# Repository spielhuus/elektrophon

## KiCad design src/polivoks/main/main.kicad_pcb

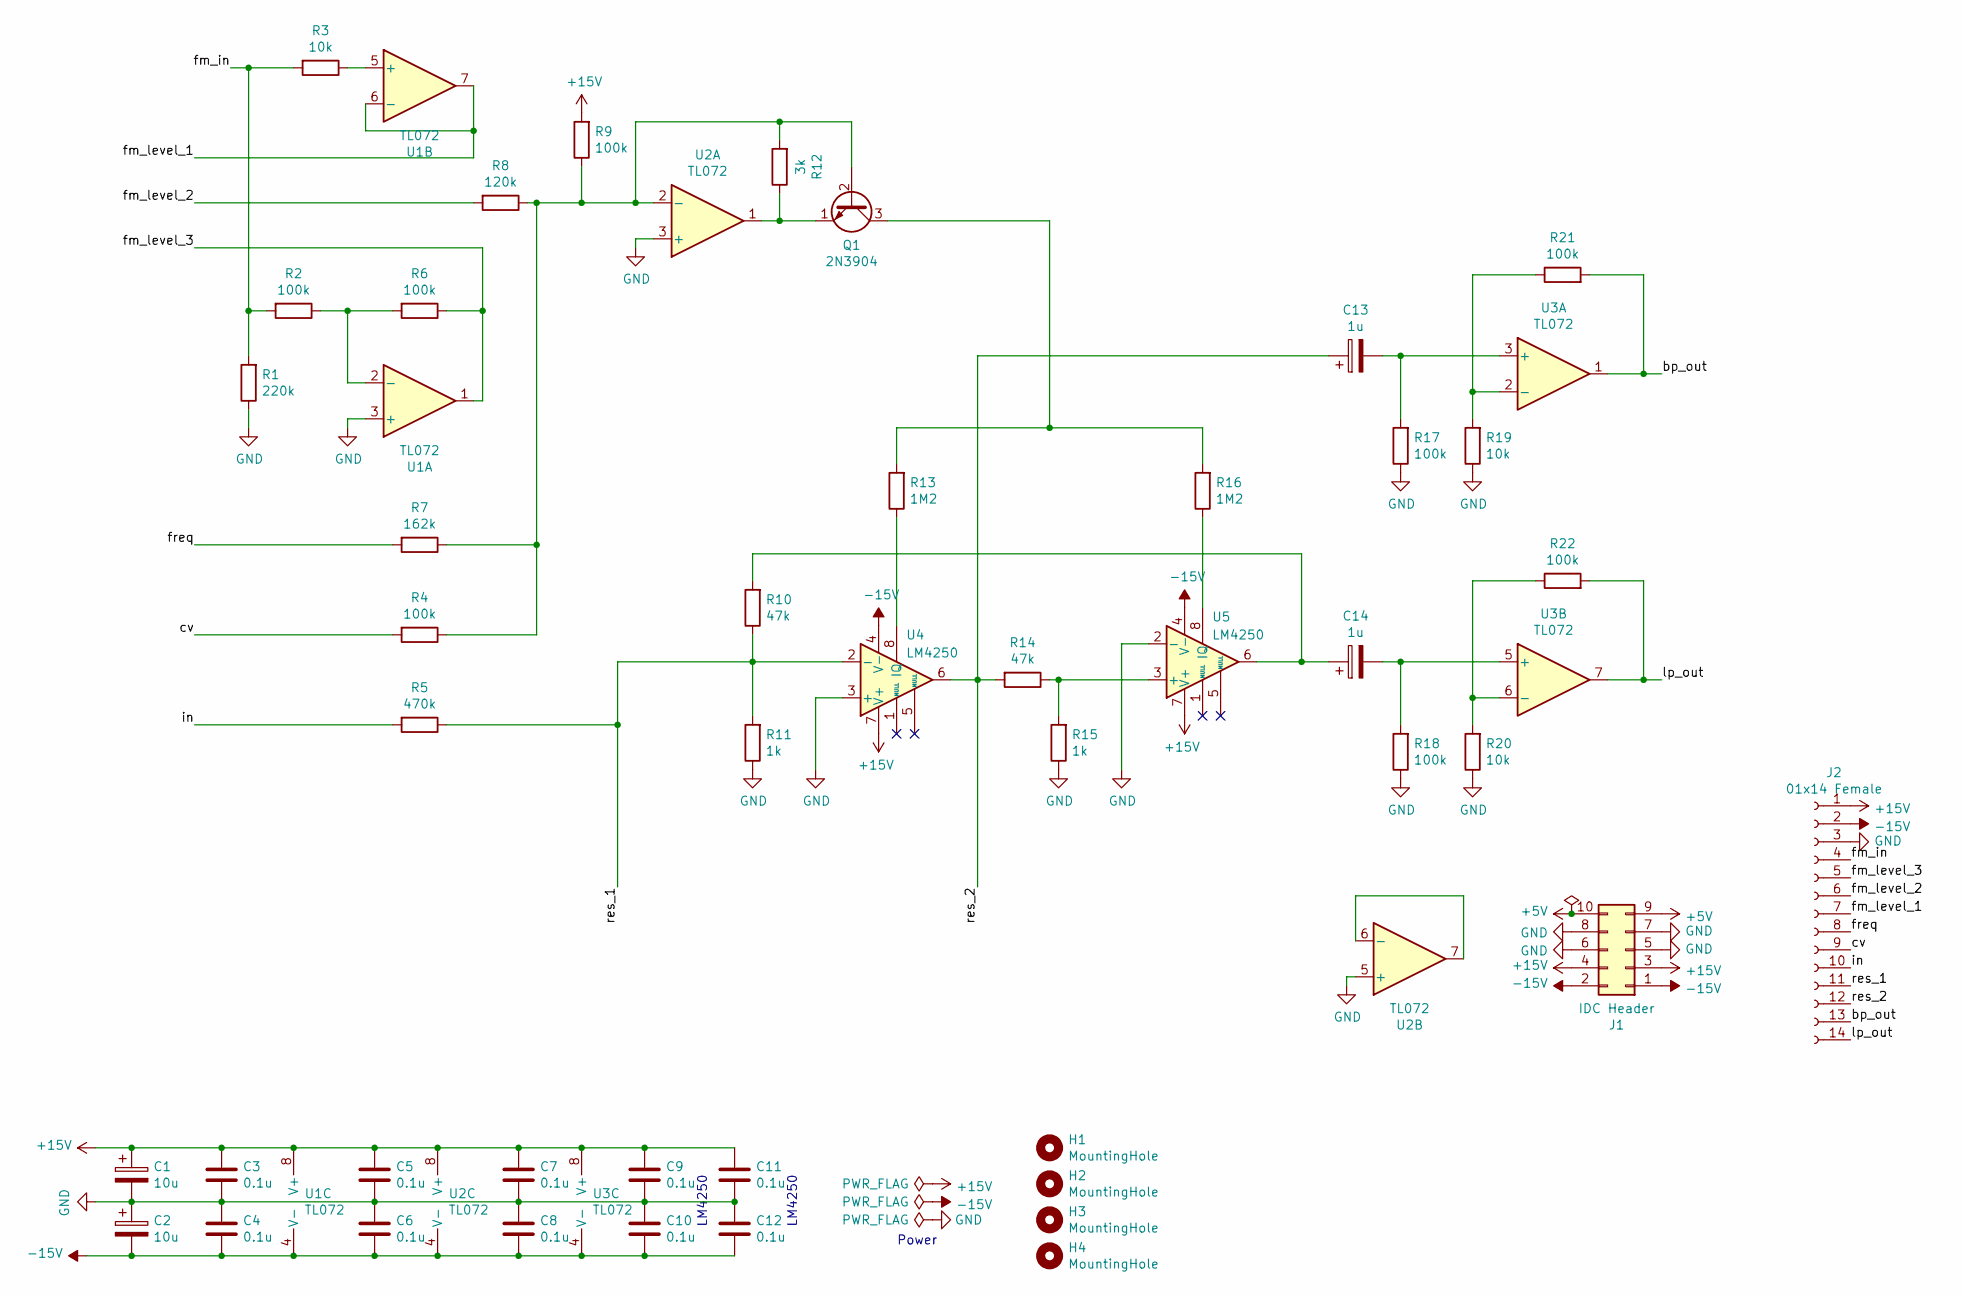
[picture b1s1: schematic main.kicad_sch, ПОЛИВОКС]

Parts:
C1, C2: 10u; CP_Radial_D5.0mm_P2.50mm
C3, C4, C5, C6, C7, C8, C9, C10, C11, C12: 0.1u; C_Disc_D3.4mm_W2.1mm_P2.50mm
C13, C14: 1u; CP_Radial_D5.0mm_P2.00mm
H1, H2, H3, H4: MountingHole; MountingHole_2.2mm_M2
J1: IDC Header; IDC-Header_2x05_P2.54mm_Vertical
J2: 01x14 Female; PinSocket_1x14_P2.54mm_Vertical
Q1: 2N3904; TO-92_Inline_Wide
R1: 220k; R_Axial_DIN0207_L6.3mm_D2.5mm_P10.16mm_Horizontal
R2, R4, R9, R17, R18: 100k; R_Axial_DIN0207_L6.3mm_D2.5mm_P10.16mm_Horizontal
R3, R19, R20: 10k; R_Axial_DIN0207_L6.3mm_D2.5mm_P10.16mm_Horizontal
R5: 470k; R_Axial_DIN0207_L6.3mm_D2.5mm_P10.16mm_Horizontal
R6, R21, R22: 100k; R_Axial_DIN0207_L6.3mm_D2.5mm_P2.54mm_Vertical
R7: 162k; R_Axial_DIN0207_L6.3mm_D2.5mm_P10.16mm_Horizontal
R8: 120k; R_Axial_DIN0207_L6.3mm_D2.5mm_P10.16mm_Horizontal
R10, R14: 47k; R_Axial_DIN0207_L6.3mm_D2.5mm_P10.16mm_Horizontal
R11, R15: 1k; R_Axial_DIN0207_L6.3mm_D2.5mm_P10.16mm_Horizontal
R12: 3k; R_Axial_DIN0207_L6.3mm_D2.5mm_P10.16mm_Horizontal
R13, R16: 1M2; R_Axial_DIN0207_L6.3mm_D2.5mm_P10.16mm_Horizontal
U1, U2, U3: TL072; DIP-8_W7.62mm_Socket
U4, U5: LM4250; DIP-8_W7.62mm_Socket

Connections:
+5V: J1.9, J1.10
+15V: C1.1, C3.1, C5.1, C7.1, C9.1, C11.1, J1.3, J1.4, J2.1, R9.2, U1.8 (V+), U2.8 (V+), U3.8 (V+), U4.7 (V+), U5.7 (V+)
-15V: C2.2, C4.2, C6.2, C8.2, C10.2, C12.2, J1.1, J1.2, J2.2, U1.4 (V-), U2.4 (V-), U3.4 (V-), U4.4 (V-), U5.4 (V-)
/bp_out: J2.13, R21.2, U3.1
/cv: J2.9, R4.2
/fm_in: J2.4, R1.2, R2.2, R3.2
/fm_level_1: J2.7, U1.6 (-), U1.7
/fm_level_2: J2.6, R8.2
/fm_level_3: J2.5, R6.1, U1.1
/freq: J2.8, R7.2
/in: J2.10, R5.2
/lp_out: J2.14, R22.2, U3.7
/res_1: J2.11, R5.1, R10.1, R11.2, U4.2 (-)
/res_2: C13.1, J2.12, R14.2, U4.6
GND: C1.2, C2.1, C3.2, C4.1, C5.2, C6.1, C7.2, C8.1, C9.2, C10.1, C11.2, C12.1, J1.5, J1.6, J1.7, J1.8, J2.3, R1.1, R11.1, R15.1, R17.1, R18.1, R19.1, R20.1, U1.3 (+), U2.3 (+), U2.5 (+), U4.3 (+), U5.2 (-)
unnamed: C14.1, R10.2, U5.6
unnamed: Q1.2 (B), R4.1, R7.1, R8.1, R9.1, R12.2, U2.2 (-)
unnamed: Q1.3 (C), R13.2, R16.2
unnamed: Q1.1 (E), R12.1, U2.1
unnamed: R2.1, R6.2, U1.2 (-)
unnamed: R3.1, U1.5 (+)
unnamed: U2.6 (-), U2.7
unnamed: C13.2, R17.2, U3.3 (+)
unnamed: R19.2, R21.1, U3.2 (-)
unnamed: C14.2, R18.2, U3.5 (+)
unnamed: R20.2, R22.1, U3.6 (-)
unnamed: R13.1, U4.8 (IQ)
unnamed: R14.1, R15.2, U5.3 (+)
unnamed: R16.1, U5.8 (IQ)

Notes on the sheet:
LM4250
Power

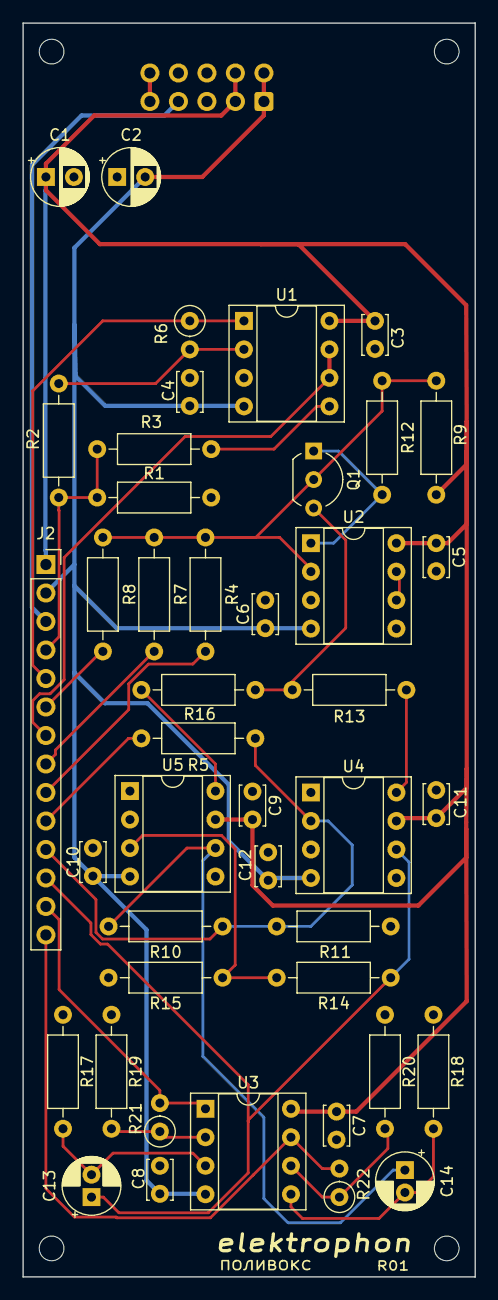
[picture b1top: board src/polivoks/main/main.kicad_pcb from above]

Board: 2 copper layers, 40.3 x 111.8 mm, 48 parts (1 on the bottom side), 29 nets.

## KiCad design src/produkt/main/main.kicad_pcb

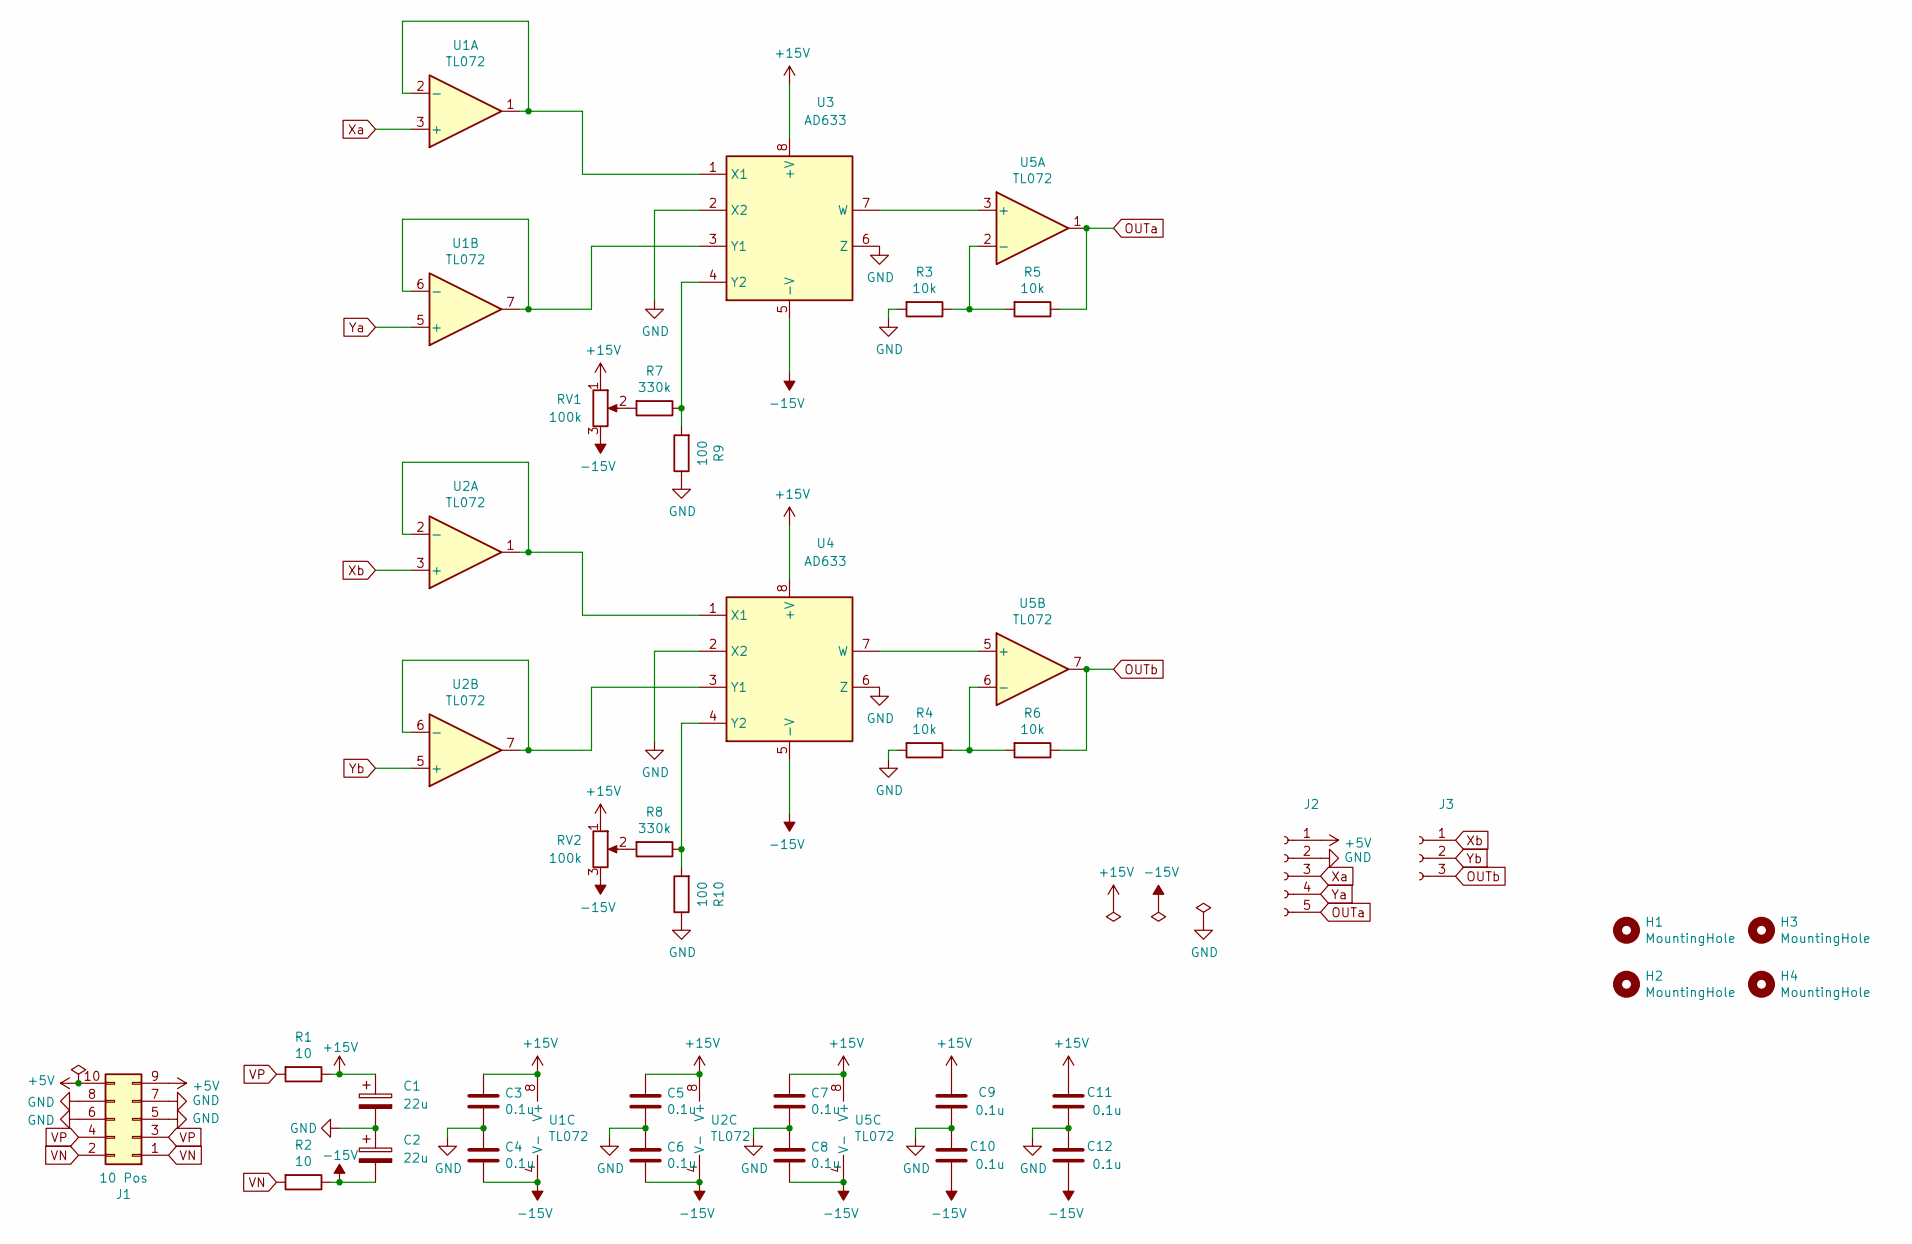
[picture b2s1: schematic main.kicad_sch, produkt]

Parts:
C1, C2: 22u; CP_Radial_D6.3mm_P2.50mm
C3, C4, C5, C6, C7, C8, C9, C10, C11, C12: 0.1u; C_Disc_D3.8mm_W2.6mm_P2.50mm
H1, H2, H3, H4: MountingHole; MountingHole_2.2mm_M2
J1: 10 Pos; IDC-Header_2x05_P2.54mm_Vertical
J2: 01x05 Female; PinSocket_1x05_P2.54mm_Vertical
J3: 01x03 Female; PinSocket_1x03_P2.54mm_Vertical
R1, R2: 10; R_Axial_DIN0204_L3.6mm_D1.6mm_P5.08mm_Horizontal
R3, R4, R5, R6: 10k; R_Axial_DIN0204_L3.6mm_D1.6mm_P5.08mm_Horizontal
R7, R8: 330k; R_Axial_DIN0204_L3.6mm_D1.6mm_P5.08mm_Horizontal
R9, R10: 100; R_Axial_DIN0204_L3.6mm_D1.6mm_P5.08mm_Horizontal
RV1, RV2: 100k; Potentiometer_Bourns_3386P_Vertical
U1, U2, U5: TL072; DIP-8_W7.62mm_Socket
U3, U4: AD633; DIP-8_W7.62mm

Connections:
+5V: J1.9, J1.10, J2.1
+15V: C1.1, C3.1, C5.1, C7.1, C9.1, C11.1, R1.1, RV1.1, RV2.1, U1.8 (V+), U2.8 (V+), U3.8 (+V), U4.8 (+V), U5.8 (V+)
-15V: C2.2, C4.2, C6.2, C8.2, C10.2, C12.2, R2.1, RV1.3, RV2.3, U1.4 (V-), U2.4 (V-), U3.5 (-V), U4.5 (-V), U5.4 (V-)
GND: C1.2, C2.1, C3.2, C4.1, C5.2, C6.1, C7.2, C8.1, C9.2, C10.1, C11.2, C12.1, J1.5, J1.6, J1.7, J1.8, J2.2, R3.2, R4.2, R9.1, R10.1, U3.2 (X2), U3.6 (Z), U4.2 (X2), U4.6 (Z)
unnamed: R7.2, RV1.2
unnamed: R8.2, RV2.2
unnamed: U1.1, U1.2 (-), U3.1 (X1)
unnamed: U1.6 (-), U1.7, U3.3 (Y1)
unnamed: U2.1, U2.2 (-), U4.1 (X1)
unnamed: U2.6 (-), U2.7, U4.3 (Y1)
unnamed: U3.7 (W), U5.3 (+)
unnamed: R7.1, R9.2, U3.4 (Y2)
unnamed: U4.7 (W), U5.5 (+)
unnamed: R8.1, R10.2, U4.4 (Y2)
unnamed: R3.1, R5.2, U5.2 (-)
unnamed: R4.1, R6.2, U5.6 (-)
OUTa: J2.5, R5.1, U5.1
OUTb: J3.3, R6.1, U5.7
VN: J1.1, J1.2, R2.2
VP: J1.3, J1.4, R1.2
Xa: J2.3, U1.3 (+)
Xb: J3.1, U2.3 (+)
Ya: J2.4, U1.5 (+)
Yb: J3.2, U2.5 (+)

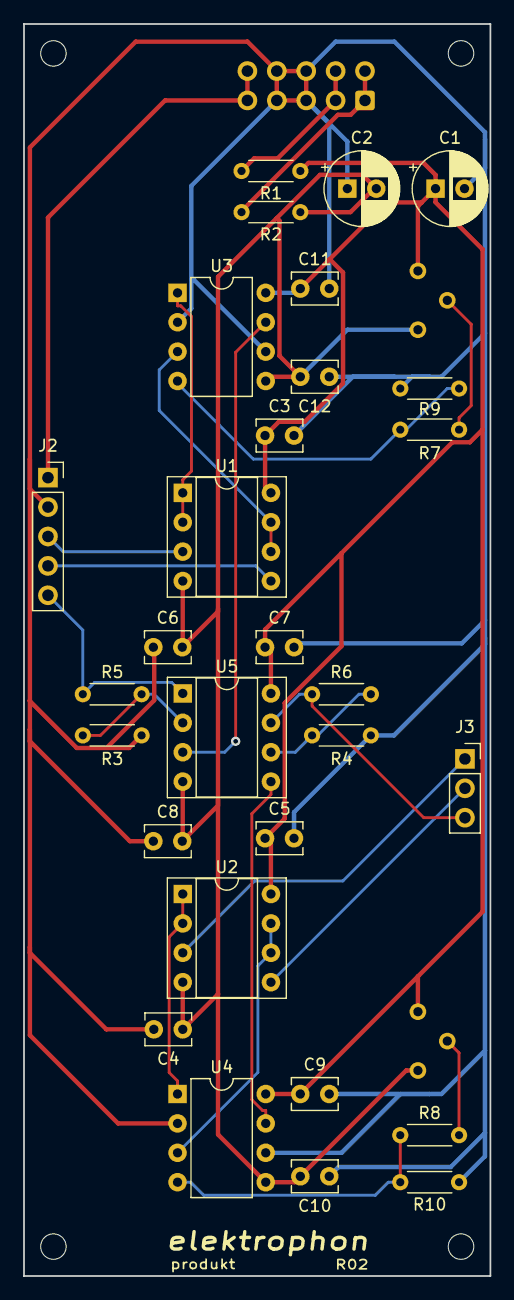
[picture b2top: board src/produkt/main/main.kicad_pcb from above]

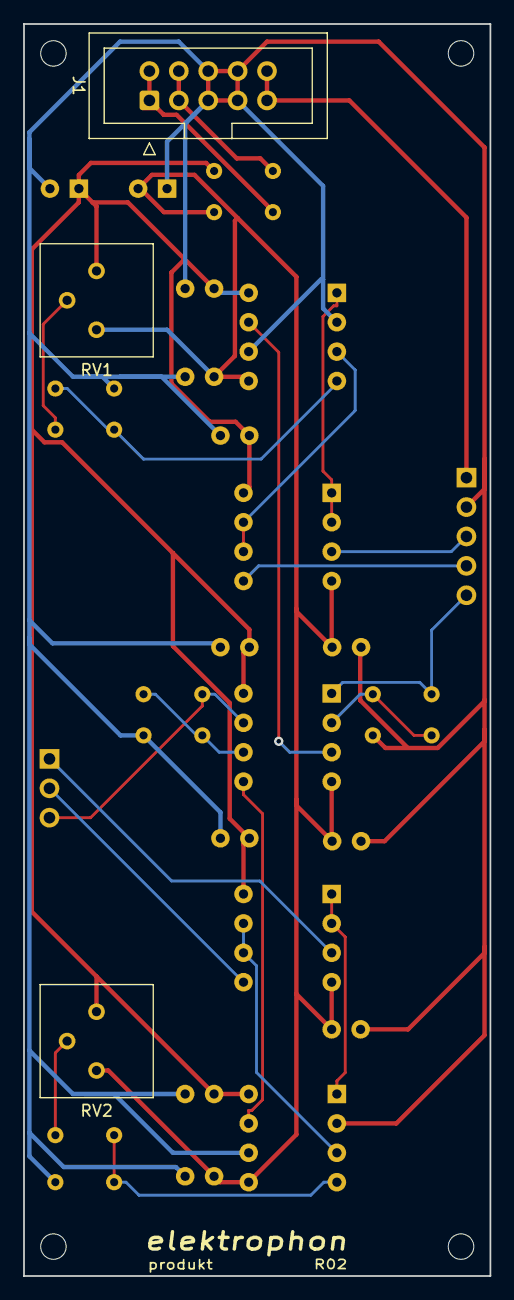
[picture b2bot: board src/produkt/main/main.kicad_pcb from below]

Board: 2 copper layers, 40.3 x 108.2 mm, 36 parts (3 on the bottom side), 24 nets.

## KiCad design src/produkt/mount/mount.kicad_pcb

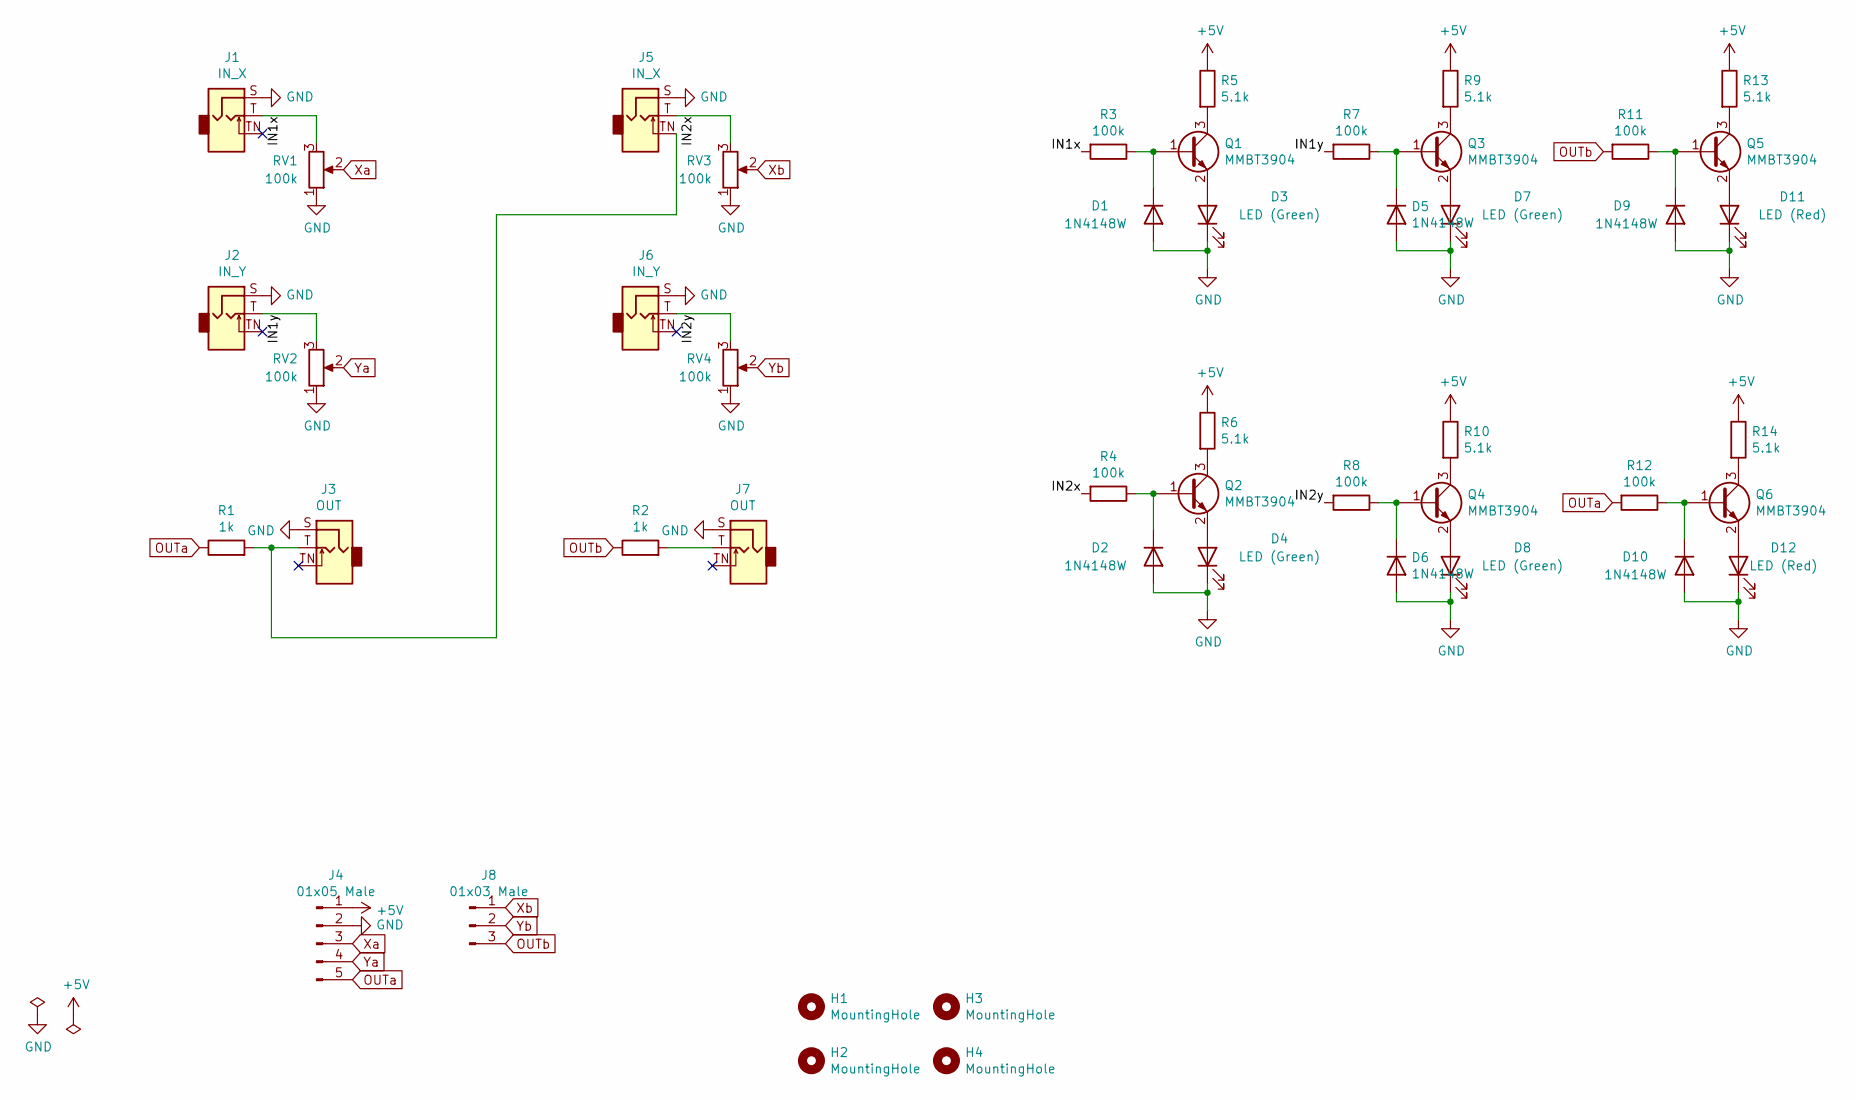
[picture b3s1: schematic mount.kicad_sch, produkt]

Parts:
D1, D2, D5, D6, D9, D10: 1N4148W; D_SOD-123
D3, D4, D7, D8: LED (Green); LED_D3.0mm
D11, D12: LED (Red); LED_D3.0mm
H1, H2, H3, H4: MountingHole; MountingHole_2.2mm_M2
J1, J5: IN_X; Jack_3.5mm_WQP-PJ398SM_Vertical
J2, J6: IN_Y; Jack_3.5mm_WQP-PJ398SM_Vertical
J3, J7: OUT; Jack_3.5mm_WQP-PJ398SM_Vertical
J4: 01x05 Male; PinHeader_1x05_P2.54mm_Vertical
J8: 01x03 Male; PinHeader_1x03_P2.54mm_Vertical
Q1, Q2, Q3, Q4, Q5, Q6: MMBT3904; SOT-23
R1, R2: 1k; R_Axial_DIN0204_L3.6mm_D1.6mm_P5.08mm_Horizontal
R3, R4, R7, R8, R11, R12: 100k; R_0805_2012Metric_Pad1.20x1.40mm_HandSolder
R5, R6, R9, R10, R13, R14: 5.1k; R_0805_2012Metric_Pad1.20x1.40mm_HandSolder
RV1, RV2, RV3, RV4: 100k; Potentiometer_Alpha_RD901F-40-00D_Single_Vertical

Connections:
+5V: J4.1, R5.1, R6.1, R9.1, R10.1, R13.1, R14.1
/IN1x: J1.T, R3.2, RV1.3
/IN1y: J2.T, R7.2, RV2.3
/IN2x: J5.T, R4.2, RV3.3
/IN2y: J6.T, R8.2, RV4.3
GND: D1.2 (A), D2.2 (A), D3.1 (K), D4.1 (K), D5.2 (A), D6.2 (A), D7.1 (K), D8.1 (K), D9.2 (A), D10.2 (A), D11.1 (K), D12.1 (K), J1.S, J2.S, J3.S, J4.2, J5.S, J6.S, J7.S, RV1.1, RV2.1, RV3.1, RV4.1
unnamed: D1.1 (K), Q1.1 (B), R3.1
unnamed: D2.1 (K), Q2.1 (B), R4.1
unnamed: D3.2 (A), Q1.2 (E)
unnamed: D4.2 (A), Q2.2 (E)
unnamed: D5.1 (K), Q3.1 (B), R7.1
unnamed: D6.1 (K), Q4.1 (B), R8.1
unnamed: D7.2 (A), Q3.2 (E)
unnamed: D8.2 (A), Q4.2 (E)
unnamed: D9.1 (K), Q5.1 (B), R11.1
unnamed: D10.1 (K), Q6.1 (B), R12.1
unnamed: D11.2 (A), Q5.2 (E)
unnamed: D12.2 (A), Q6.2 (E)
unnamed: J3.T, J5.TN, R1.2
unnamed: J7.T, R2.2
unnamed: Q1.3 (C), R5.2
unnamed: Q2.3 (C), R6.2
unnamed: Q3.3 (C), R9.2
unnamed: Q4.3 (C), R10.2
unnamed: Q5.3 (C), R13.2
unnamed: Q6.3 (C), R14.2
OUTa: J4.5, R1.1, R12.2
OUTb: J8.3, R2.1, R11.2
Xa: J4.3, RV1.2
Xb: J8.1, RV3.2
Ya: J4.4, RV2.2
Yb: J8.2, RV4.2

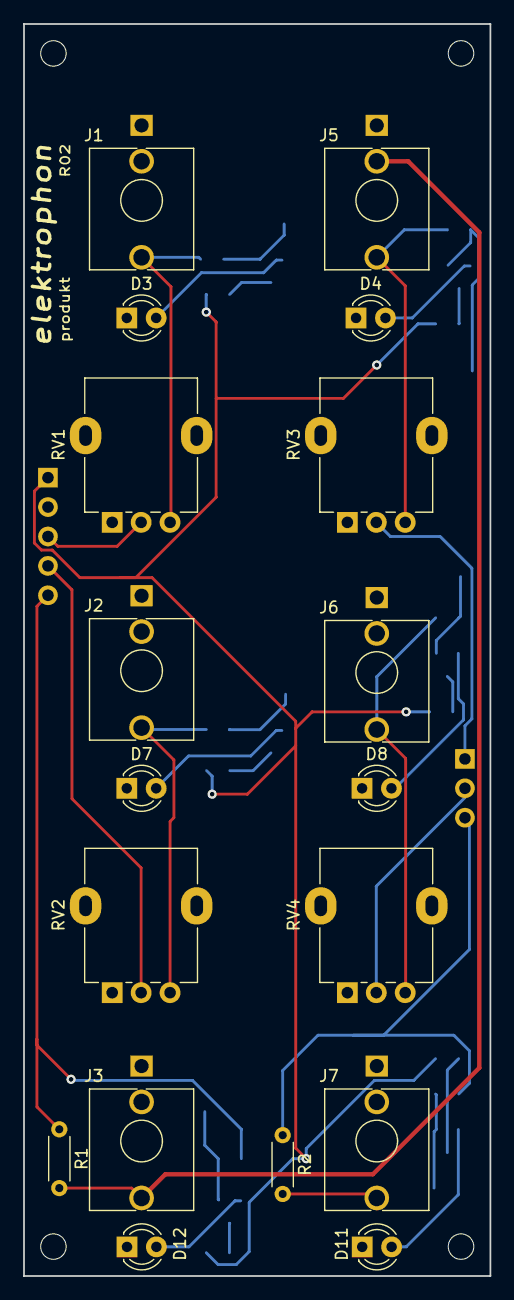
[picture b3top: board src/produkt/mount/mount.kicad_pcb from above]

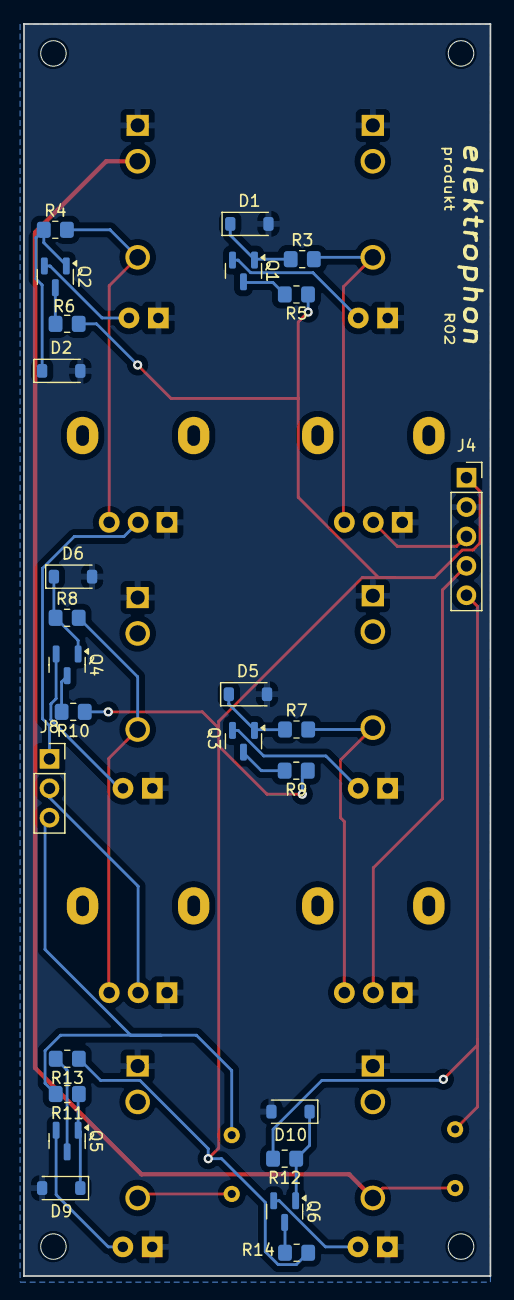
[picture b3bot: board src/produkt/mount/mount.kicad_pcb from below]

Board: 2 copper layers, 40.3 x 108.2 mm, 48 parts (26 on the bottom side), 32 nets.

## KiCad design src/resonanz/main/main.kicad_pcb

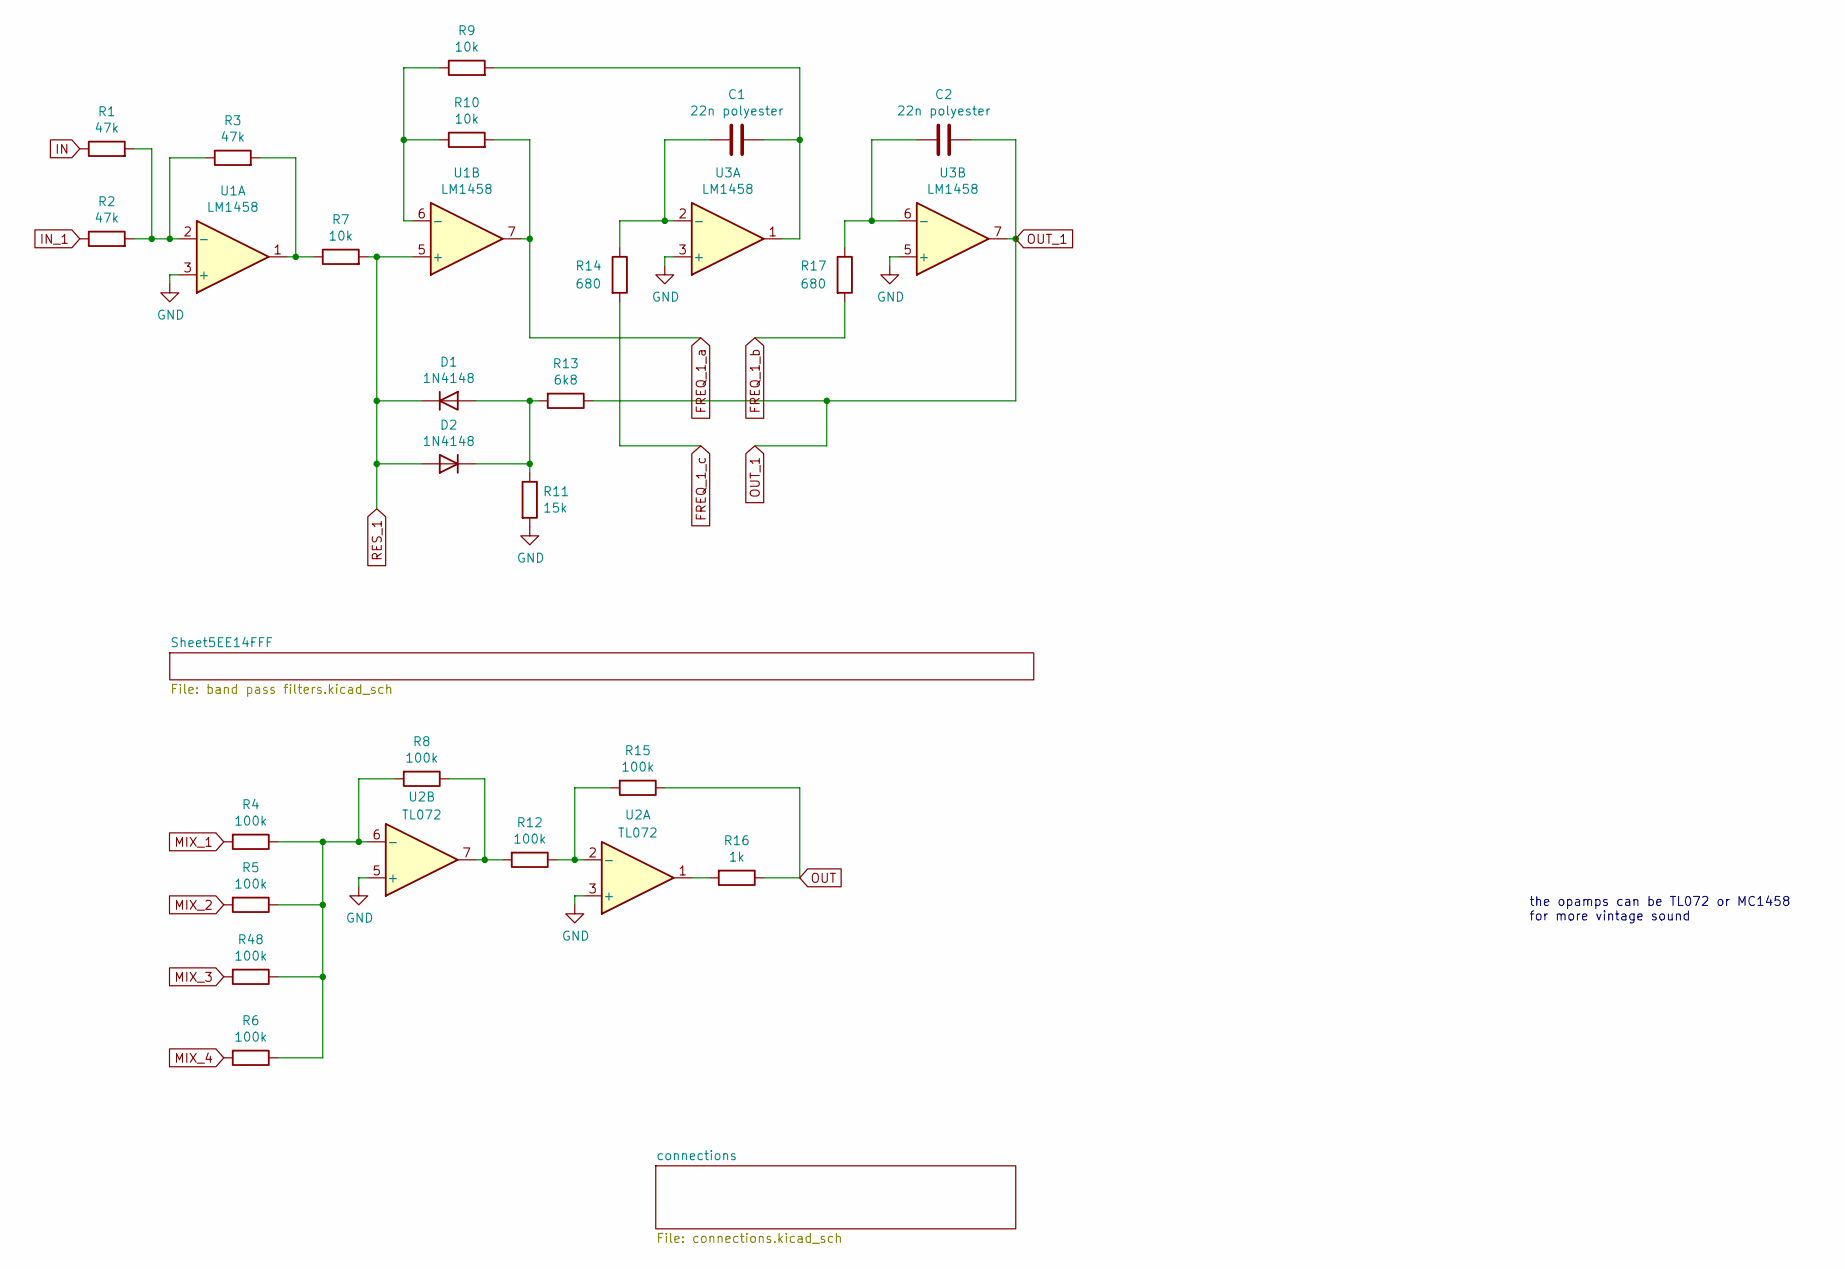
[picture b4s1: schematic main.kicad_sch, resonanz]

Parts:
C1, C2: 22n polyester; C_Rect_L7.2mm_W2.5mm_P5.00mm_FKS2_FKP2_MKS2_MKP2
D1, D2: 1N4148; D_DO-35_SOD27_P3.81mm_Vertical_KathodeUp
R1, R2: 47k; R_Axial_DIN0207_L6.3mm_D2.5mm_P10.16mm_Horizontal
R3: 47k; R_Axial_DIN0207_L6.3mm_D2.5mm_P2.54mm_Vertical
R4, R5, R6, R12, R15, R48: 100k; R_Axial_DIN0207_L6.3mm_D2.5mm_P10.16mm_Horizontal
R7: 10k; R_Axial_DIN0207_L6.3mm_D2.5mm_P10.16mm_Horizontal
R8: 100k; R_Axial_DIN0207_L6.3mm_D2.5mm_P2.54mm_Vertical
R9, R10: 10k; R_Axial_DIN0207_L6.3mm_D2.5mm_P2.54mm_Vertical
R11: 15k; R_Axial_DIN0207_L6.3mm_D2.5mm_P10.16mm_Horizontal
R13: 6k8; R_Axial_DIN0207_L6.3mm_D2.5mm_P2.54mm_Vertical
R14, R17: 680; R_Axial_DIN0207_L6.3mm_D2.5mm_P10.16mm_Horizontal
R16: 1k; R_Axial_DIN0207_L6.3mm_D2.5mm_P10.16mm_Horizontal
U1, U3: LM1458; DIP-8_W7.62mm_Socket
U2: TL072; DIP-8_W7.62mm_Socket

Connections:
FREQ_1_a: R10.2, U1.7; also elsewhere on the board
FREQ_1_b: R17.2; also elsewhere on the board
FREQ_1_c: R14.2; also elsewhere on the board
GND: R11.2, U1.3 (+), U2.3 (+), U2.5 (+), U3.3 (+), U3.5 (+); also elsewhere on the board
IN: R1.1; also elsewhere on the board
IN_1: R2.1; also elsewhere on the board
MIX_1: R4.2; also elsewhere on the board
MIX_2: R5.2; also elsewhere on the board
MIX_3: R48.2; also elsewhere on the board
MIX_4: R6.2; also elsewhere on the board
unnamed: C1.1, R9.2, U3.1
unnamed: D1.2 (A), D2.1 (K), R11.1, R13.2
unnamed: R3.2, R7.1, U1.1
unnamed: R8.1, R12.2, U2.7
unnamed: R16.2, U2.1
unnamed: R1.2, R2.2, R3.1, U1.2 (-)
unnamed: R9.1, R10.1, U1.6 (-)
unnamed: R12.1, R15.2, U2.2 (-)
unnamed: R4.1, R5.1, R6.1, R8.2, R48.1, U2.6 (-)
unnamed: C1.2, R14.1, U3.2 (-)
unnamed: C2.2, R17.1, U3.6 (-)
OUT: R15.1, R16.1; also elsewhere on the board
OUT_1: C2.1, R13.1, U3.7; also elsewhere on the board
RES_1: D1.1 (K), D2.2 (A), R7.2, U1.5 (+); also elsewhere on the board

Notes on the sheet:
the opamps can be TL072 or MC1458 for more vintage sound

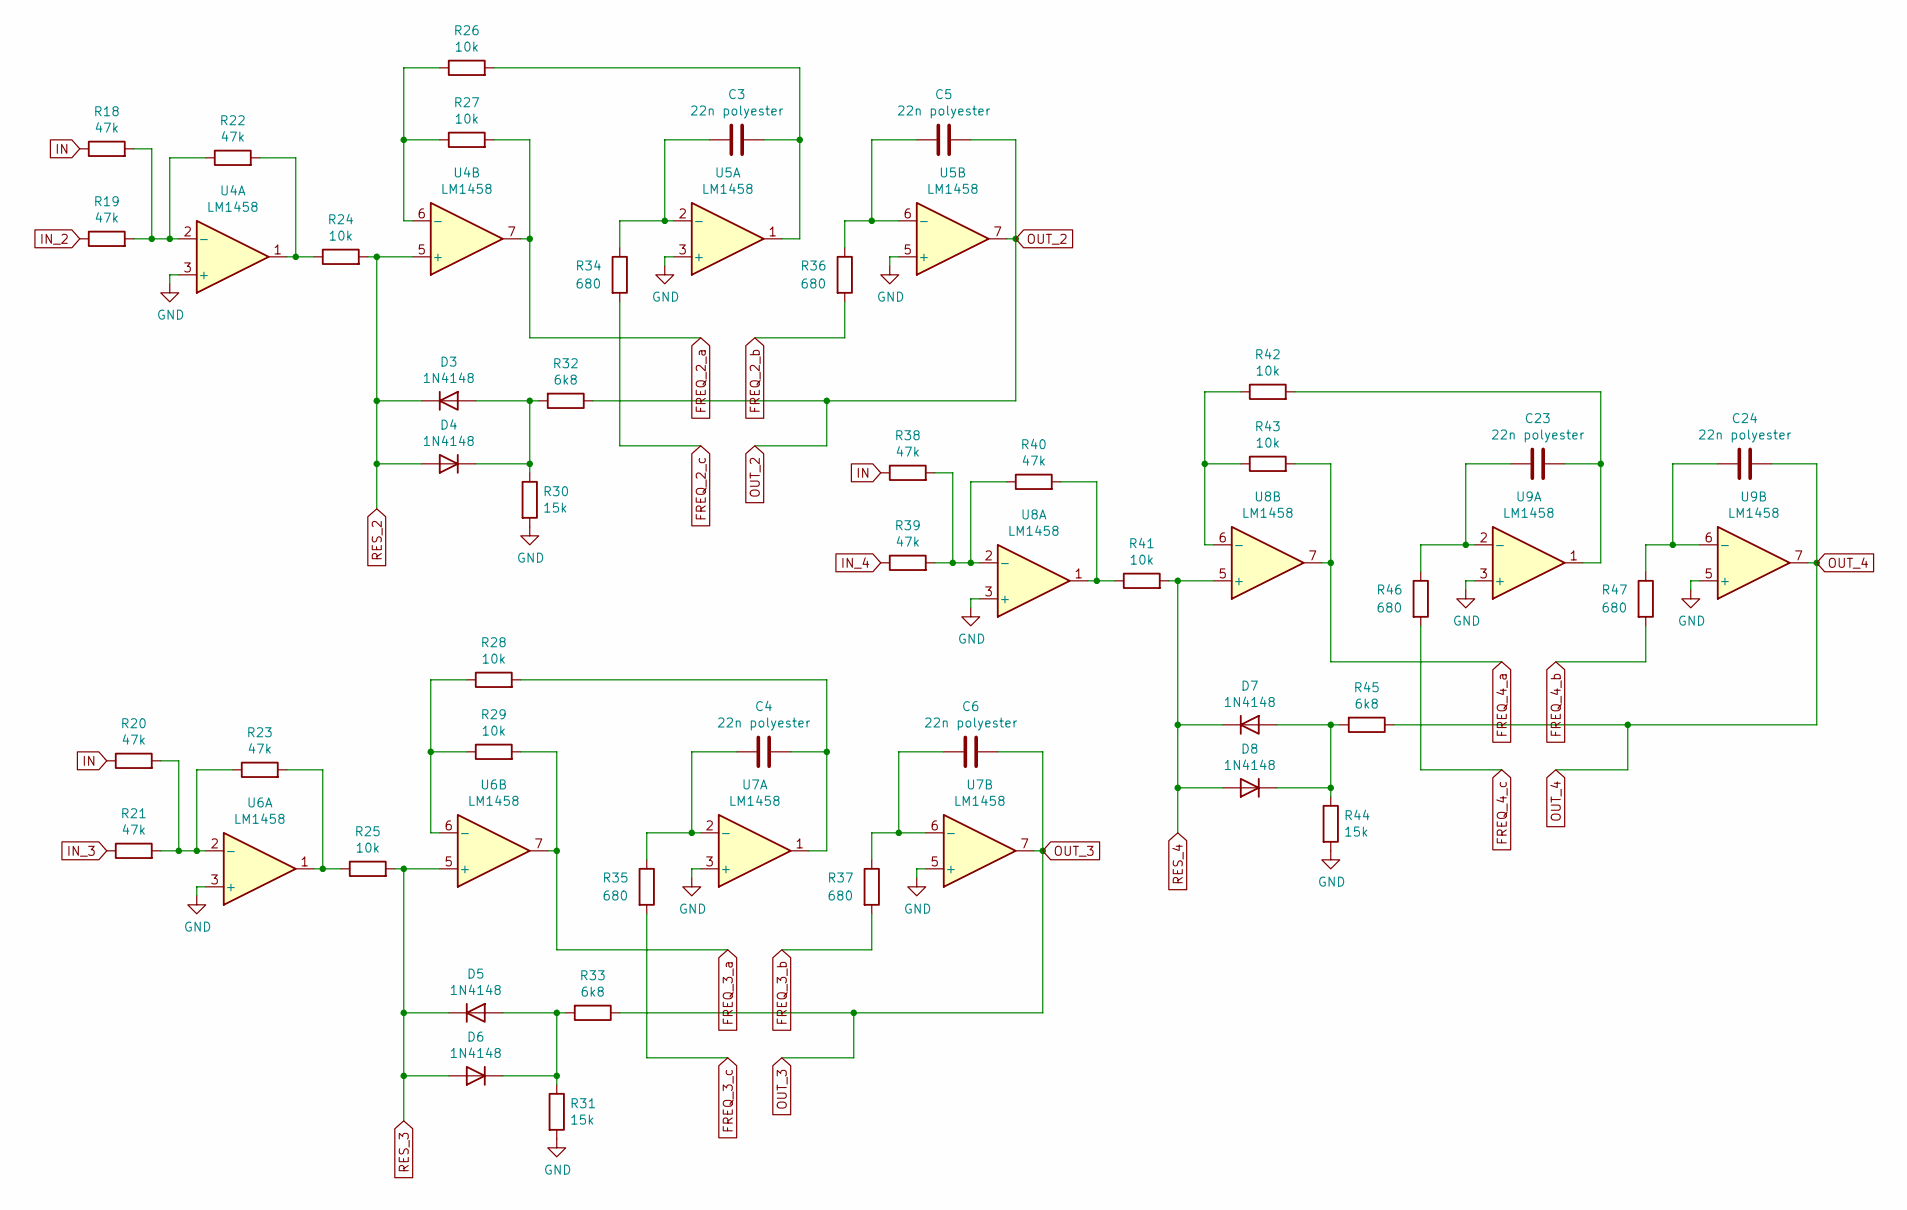
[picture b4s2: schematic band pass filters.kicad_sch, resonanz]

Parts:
C3, C4, C5, C6, C23, C24: 22n polyester; C_Rect_L7.2mm_W2.5mm_P5.00mm_FKS2_FKP2_MKS2_MKP2
D3, D4, D5, D6, D7, D8: 1N4148; D_DO-35_SOD27_P3.81mm_Vertical_KathodeUp
R18, R19, R20, R21, R38, R39: 47k; R_Axial_DIN0207_L6.3mm_D2.5mm_P10.16mm_Horizontal
R22, R23, R40: 47k; R_Axial_DIN0207_L6.3mm_D2.5mm_P2.54mm_Vertical
R24, R25, R41: 10k; R_Axial_DIN0207_L6.3mm_D2.5mm_P10.16mm_Horizontal
R26, R27, R28, R29, R42, R43: 10k; R_Axial_DIN0207_L6.3mm_D2.5mm_P2.54mm_Vertical
R30, R31, R44: 15k; R_Axial_DIN0207_L6.3mm_D2.5mm_P10.16mm_Horizontal
R32, R33, R45: 6k8; R_Axial_DIN0207_L6.3mm_D2.5mm_P2.54mm_Vertical
R34, R35, R36, R37, R46, R47: 680; R_Axial_DIN0207_L6.3mm_D2.5mm_P10.16mm_Horizontal
U4, U5, U6, U7, U8, U9: LM1458; DIP-8_W7.62mm_Socket

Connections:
FREQ_2_a: R27.2, U4.7; also elsewhere on the board
FREQ_2_b: R36.2; also elsewhere on the board
FREQ_2_c: R34.2; also elsewhere on the board
FREQ_3_a: R29.2, U6.7; also elsewhere on the board
FREQ_3_b: R37.2; also elsewhere on the board
FREQ_3_c: R35.2; also elsewhere on the board
FREQ_4_a: R43.2, U8.7; also elsewhere on the board
FREQ_4_b: R47.2; also elsewhere on the board
FREQ_4_c: R46.2; also elsewhere on the board
GND: R30.2, R31.2, R44.2, U4.3 (+), U5.3 (+), U5.5 (+), U6.3 (+), U7.3 (+), U7.5 (+), U8.3 (+), U9.3 (+), U9.5 (+); also elsewhere on the board
IN: R18.1, R20.1, R38.1; also elsewhere on the board
IN_2: R19.1; also elsewhere on the board
IN_3: R21.1; also elsewhere on the board
IN_4: R39.1; also elsewhere on the board
unnamed: C3.1, R26.2, U5.1
unnamed: C4.1, R28.2, U7.1
unnamed: C23.1, R42.2, U9.1
unnamed: D3.2 (A), D4.1 (K), R30.1, R32.2
unnamed: D5.2 (A), D6.1 (K), R31.1, R33.2
unnamed: D7.2 (A), D8.1 (K), R44.1, R45.2
unnamed: R22.2, R24.1, U4.1
unnamed: R23.2, R25.1, U6.1
unnamed: R40.2, R41.1, U8.1
unnamed: R18.2, R19.2, R22.1, U4.2 (-)
unnamed: R26.1, R27.1, U4.6 (-)
unnamed: C3.2, R34.1, U5.2 (-)
unnamed: C5.2, R36.1, U5.6 (-)
unnamed: R20.2, R21.2, R23.1, U6.2 (-)
unnamed: R28.1, R29.1, U6.6 (-)
unnamed: C4.2, R35.1, U7.2 (-)
unnamed: C6.2, R37.1, U7.6 (-)
unnamed: R38.2, R39.2, R40.1, U8.2 (-)
unnamed: R42.1, R43.1, U8.6 (-)
unnamed: C23.2, R46.1, U9.2 (-)
unnamed: C24.2, R47.1, U9.6 (-)
OUT_2: C5.1, R32.1, U5.7; also elsewhere on the board
OUT_3: C6.1, R33.1, U7.7; also elsewhere on the board
OUT_4: C24.1, R45.1, U9.7; also elsewhere on the board
RES_2: D3.1 (K), D4.2 (A), R24.2, U4.5 (+); also elsewhere on the board
RES_3: D5.1 (K), D6.2 (A), R25.2, U6.5 (+); also elsewhere on the board
RES_4: D7.1 (K), D8.2 (A), R41.2, U8.5 (+); also elsewhere on the board

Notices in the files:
src/polivoks/main/main.kicad_pcb:
License CC BY 4.0 - Attribution 4.0 International
